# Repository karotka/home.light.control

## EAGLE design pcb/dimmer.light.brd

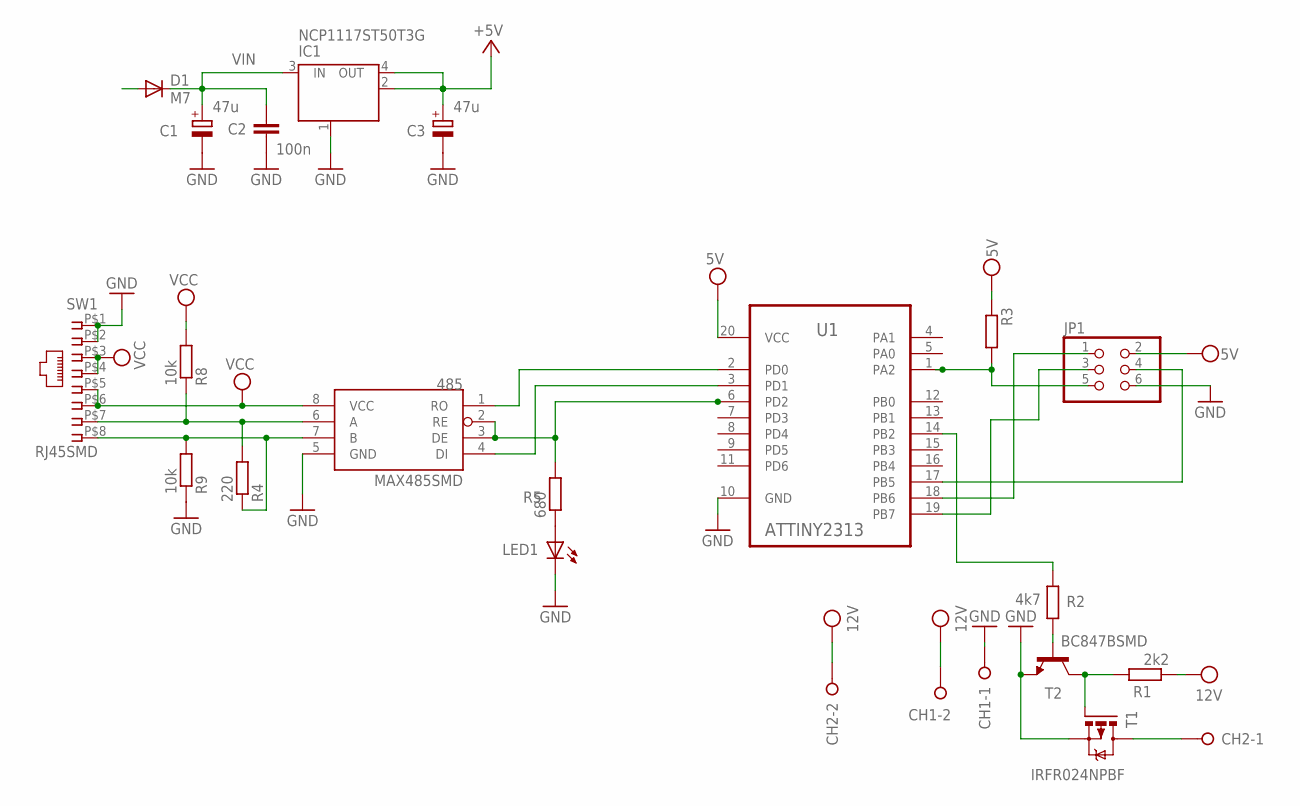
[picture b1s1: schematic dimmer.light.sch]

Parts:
485: MAX485SMD; SO08
C1, C3: 47u; PANASONIC_D
C2: 100n; C1206
CH1, CH2: W237-02P; W237-132
D1: M7; SMB
IC1: NCP1117ST50T3G; SOT223
JP1: PINHD-2X3; 2X03
LED1: LEDSML1206; SML1206
R1: 2k2; R1206
R2: 4k7; R1206
R3: R-EU_R1206; R1206
R4: 220; R1206
R5: 680; R1206
R8, R9: 10k; R1206
SW1: RJ45SMD
T1: IRFR024NPBF; D-PAK_TO252AA
T2: BC847BSMD; SOT23
U1: ATTINY2313; SOIC127P1032X265-20N

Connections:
A: 485.6 (A), R4.2, R8.1, SW1.P$7 (7)
B: 485.7 (B), R4.1, R9.2, SW1.P$8 (8)
GND: 485.5 (GND), C1.-, C2.2, C3.-, CH1.1, IC1.1 (GND/ADJ), JP1.6, LED1.C, R9.1, SW1.P$1 (1), SW1.P$2 (2), T1.3 (S), T2.2 (E), U1.10 (GND)
unnamed: R2.1, T2.1 (B)
unnamed: JP1.3, U1.19 (PB7)
unnamed: JP1.1, U1.18 (PB6)
unnamed: JP1.4, U1.17 (PB5)
unnamed: R1.2, T1.1 (G), T2.3 (C)
unnamed: R2.2, U1.14 (PB2)
unnamed: CH2.1, T1.4 (D)
unnamed: 485.4 (DI), U1.3 (PD1)
unnamed: 485.1 (RO), U1.2 (PD0)
unnamed: 485.2 (RE), 485.3 (DE), R5.2, U1.6 (PD2)
unnamed: JP1.5, R3.2, U1.1 (PA2)
unnamed: LED1.A, R5.1
PWRIN: CH1.2, CH2.2, D1.A, R1.1
VCC+5V: 485.8 (VCC), C3.+, IC1.2 (OUT), IC1.4 (OUT), JP1.2, R3.1, R8.2, SW1.P$5 (5), SW1.P$6 (6), U1.20 (VCC)
VIN: C1.+, C2.1, D1.C, IC1.3 (IN), SW1.P$3 (3), SW1.P$4 (4)

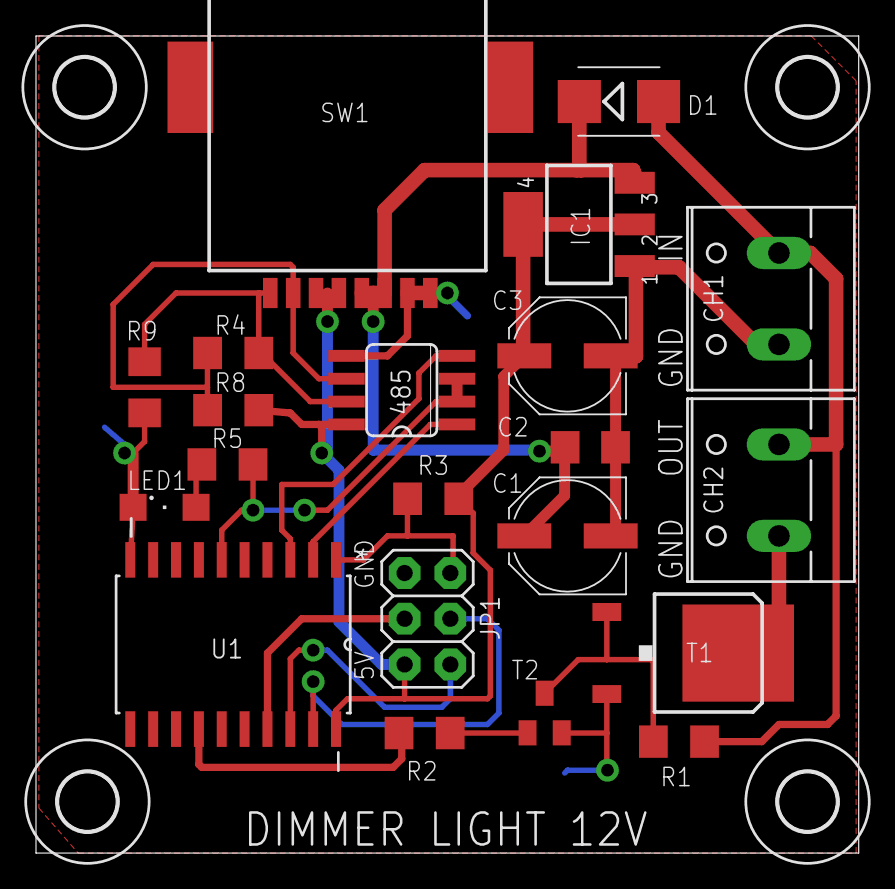
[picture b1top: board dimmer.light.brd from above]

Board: 2 copper layers, 45.7 x 45.4 mm, 25 parts (0 on the bottom side), 18 nets.

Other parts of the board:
U$1, U$2, U$3, U$4: 3,2

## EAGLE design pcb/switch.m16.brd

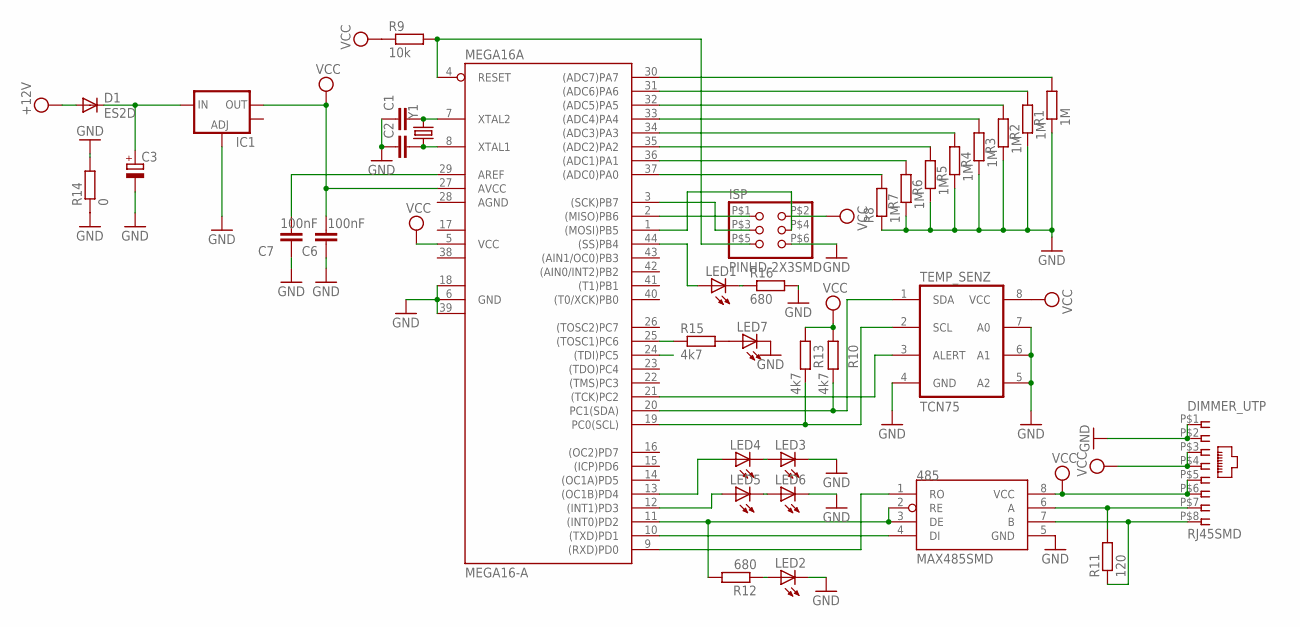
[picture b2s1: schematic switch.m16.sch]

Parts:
485: MAX485SMD; SO08
C1, C2: C-EUC0805; C0805
C3: CPOL-EUSMCC; SMC_C
C6, C7: 100nF; C1206
D1: ES2D; SMB
DIMMER_UTP: RJ45SMD
IC1: V_REG_LM1117SOT223; SOT223
ISP: PINHD-2X3SMD; 2X03SMD
LED1, LED2, LED3, LED4, LED5, LED6, LED7: LEDSML1206; SML1206
MEGA16A: MEGA16-A; TQFP44
R1, R2, R3, R4, R5, R6, R7, R8: 1M; R1206
R9: 10k; R1206
R10, R13, R15: 4k7; R1206
R11: 120; R1206
R12, R16: 680; R1206
R14: 0; R1206
TEMP_SENZ: TCN75; SO08
Y1: CRYSTAL5X3; CRYSTAL-SMD-5X3

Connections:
+12V: D1.A, DIMMER_UTP.P$3 (3), DIMMER_UTP.P$4 (4)
AGND: MEGA16A.28 (AGND)
GND: 485.5 (GND), C1.1, C2.1, C3.-, C6.1, C7.2, DIMMER_UTP.P$1 (1), DIMMER_UTP.P$2 (2), IC1.1 (ADJ), ISP.P$6 (6), LED2.C, LED3.C, LED6.C, LED7.C, MEGA16A.6 (GND), MEGA16A.18 (GND1), MEGA16A.39 (GND2), R1.1, R2.1, R3.1, R4.1, R5.1, R6.1, R7.1, R8.1, R14.1, R14.2, R16.2, TEMP_SENZ.4 (GND), TEMP_SENZ.5 (A2), TEMP_SENZ.6 (A1), TEMP_SENZ.7 (A0)
unnamed: LED4.A, MEGA16A.13 ((OC1B)PD4)
unnamed: LED1.A, MEGA16A.44 ((SS)PB4)
unnamed: C3.+, D1.C, IC1.3 (IN)
unnamed: MEGA16A.31 ((ADC6)PA6), R2.2
unnamed: MEGA16A.30 ((ADC7)PA7), R1.2
unnamed: MEGA16A.37 ((ADC0)PA0), R8.2
unnamed: MEGA16A.34 ((ADC3)PA3), R5.2
unnamed: MEGA16A.35 ((ADC2)PA2), R6.2
unnamed: MEGA16A.25 ((TOSC1)PC6), R15.1
unnamed: MEGA16A.19 (PC0(SCL)), R13.2, TEMP_SENZ.2 (SCL)
unnamed: MEGA16A.20 (PC1(SDA)), R10.2, TEMP_SENZ.1 (SDA)
unnamed: MEGA16A.21 ((TCK)PC2), TEMP_SENZ.3 (ALERT)
unnamed: LED7.A, R15.2
unnamed: 485.1 (RO), MEGA16A.9 ((RXD)PD0)
unnamed: 485.4 (DI), MEGA16A.10 ((TXD)PD1)
unnamed: 485.2 (RE), 485.3 (DE), MEGA16A.11 ((INT0)PD2), R12.2
unnamed: LED5.A, MEGA16A.12 ((INT1)PD3)
unnamed: ISP.P$1 (1), MEGA16A.2 ((MISO)PB6)
unnamed: ISP.P$3 (3), MEGA16A.3 ((SCK)PB7)
unnamed: ISP.P$5 (5), MEGA16A.4 (RESET), R9.2
unnamed: ISP.P$4 (4), MEGA16A.1 ((MOSI)PB5)
unnamed: 485.6 (A), DIMMER_UTP.P$7 (7), R11.2
unnamed: 485.7 (B), DIMMER_UTP.P$8 (8), R11.1
unnamed: C1.2, MEGA16A.7 (XTAL2), Y1.3 (2)
unnamed: C2.2, MEGA16A.8 (XTAL1), Y1.1
unnamed: LED2.A, R12.1
unnamed: MEGA16A.33 ((ADC4)PA4), R4.2
unnamed: LED1.C, R16.1
unnamed: MEGA16A.32 ((ADC5)PA5), R3.2
unnamed: MEGA16A.36 ((ADC1)PA1), R7.2
unnamed: C7.1, MEGA16A.29 (AREF)
unnamed: LED3.A, LED4.C
unnamed: LED5.C, LED6.A
PC5: MEGA16A.24 ((TDI)PC5)
VCC: 485.8 (VCC), C6.2, DIMMER_UTP.P$5 (5), DIMMER_UTP.P$6 (6), IC1.2 (OUT), ISP.P$2 (2), MEGA16A.5 (VCC), MEGA16A.27 (AVCC), R9.1, R10.1, R13.1, TEMP_SENZ.8 (VCC)
VCC1: MEGA16A.17 (VCC1)
VCC2: MEGA16A.38 (VCC2)

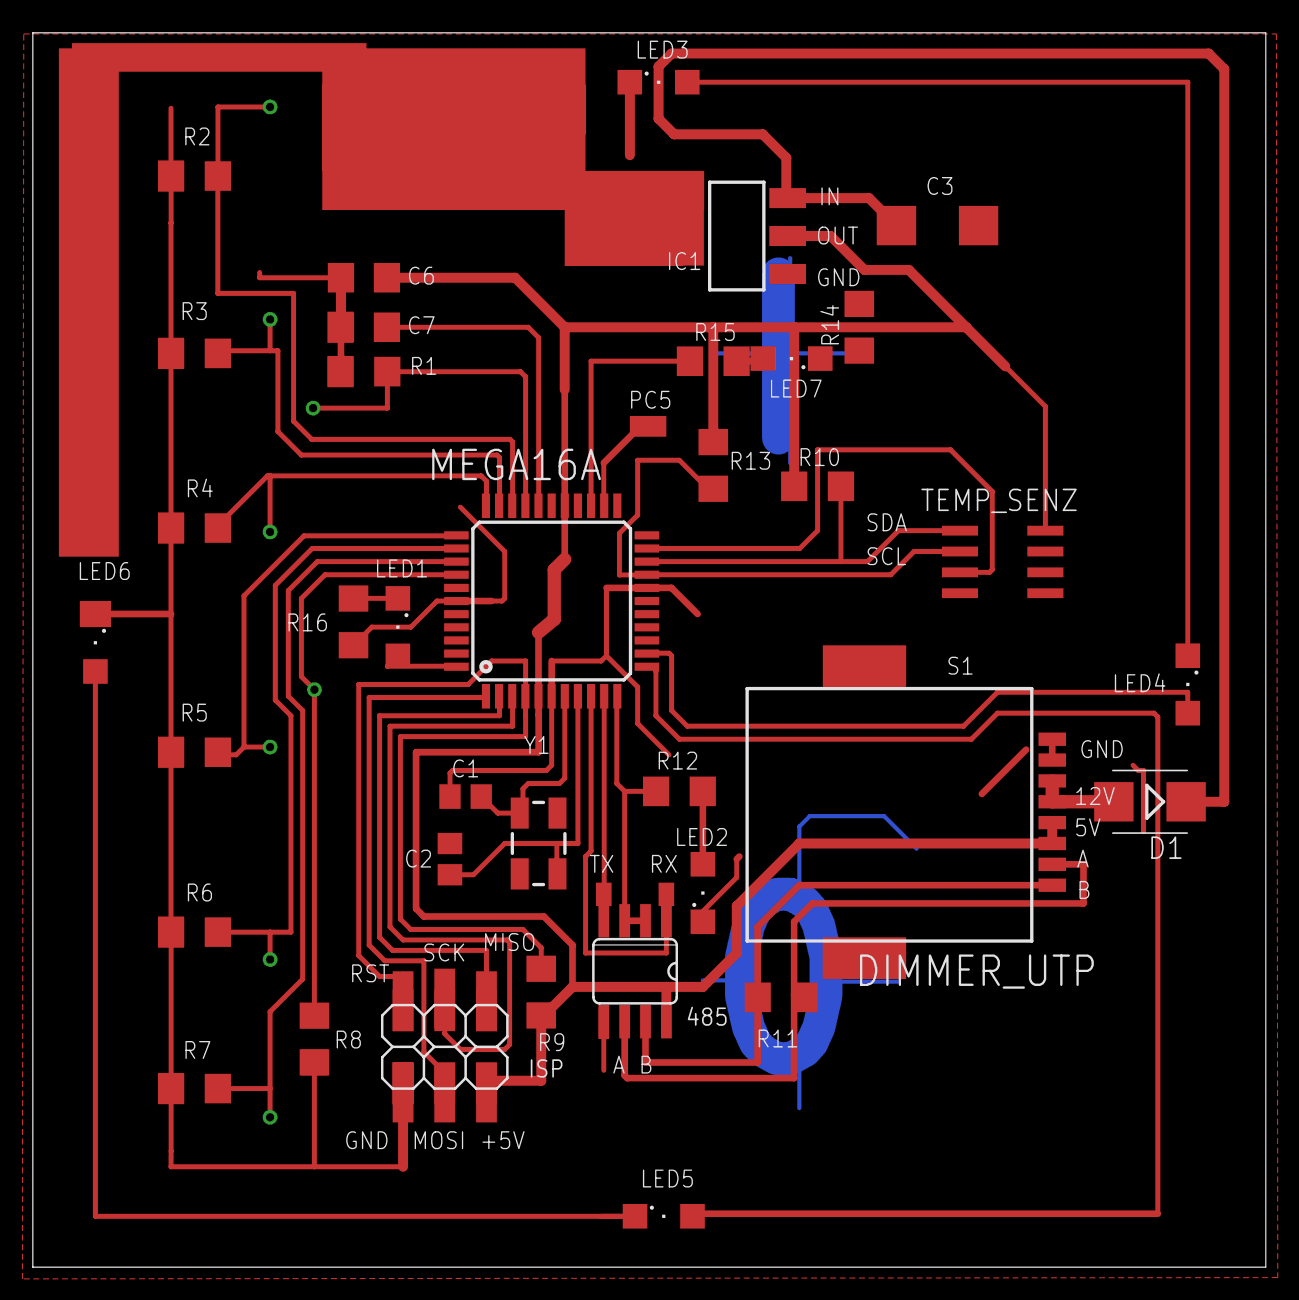
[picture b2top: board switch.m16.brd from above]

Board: 2 copper layers, 75.1 x 75.2 mm, 36 parts (0 on the bottom side), 36 nets.

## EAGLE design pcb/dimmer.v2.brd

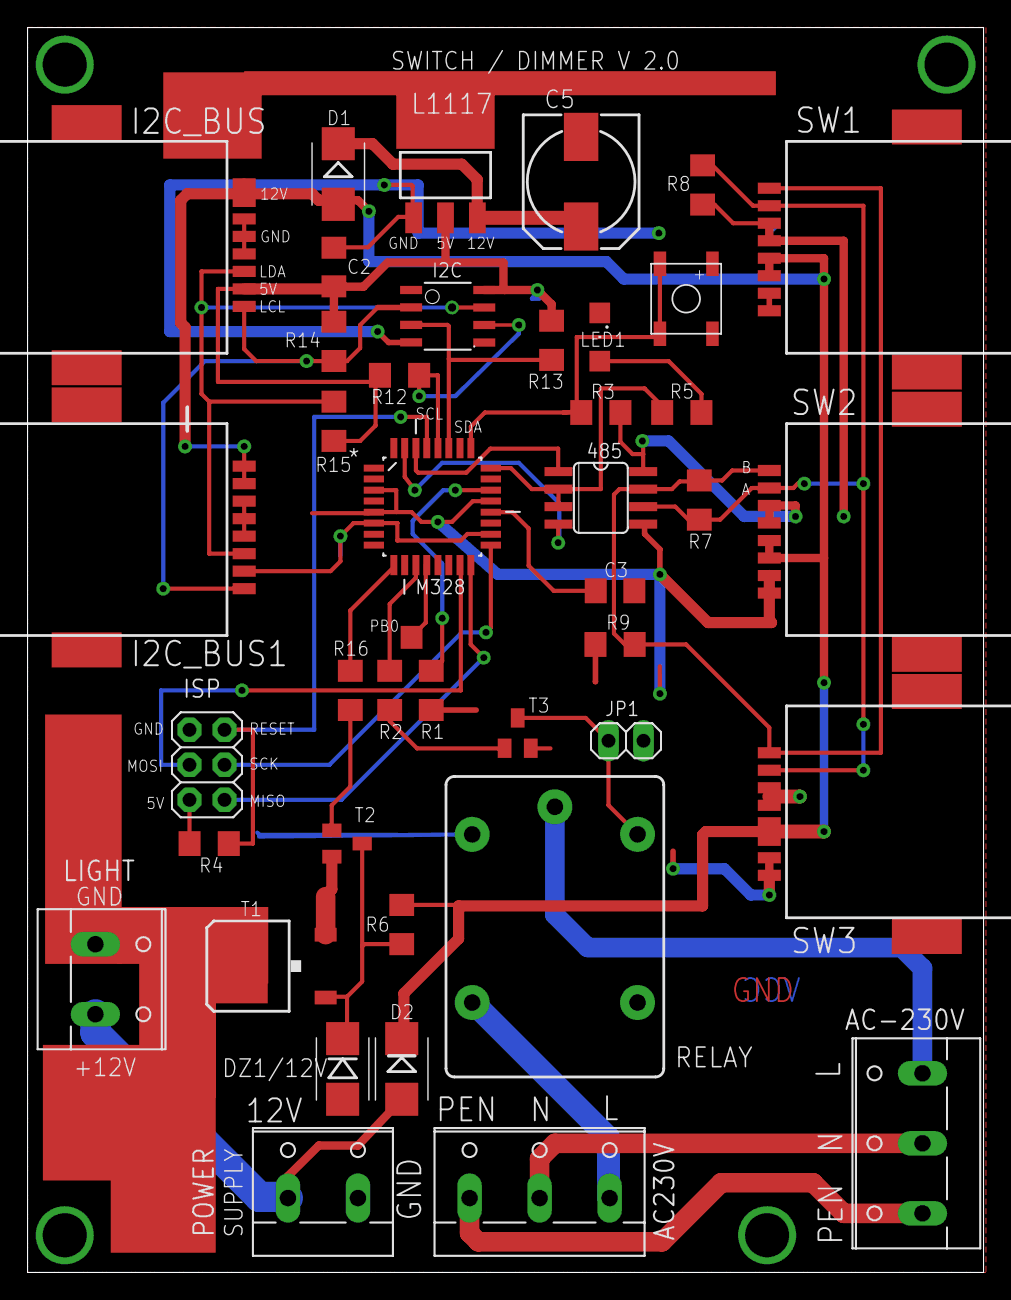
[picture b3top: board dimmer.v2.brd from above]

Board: 2 copper layers, 69.4 x 90.3 mm, 41 parts (0 on the bottom side), 33 nets.

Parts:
485: MAX485SMD; SO08
AC230V: W237-3E
AC-230V: W237-3E
C2, C3: 100nF; C1206
C5: 100uF; 140CLH-0810
D1, D2: M1; SMB
DZ1/12V: DIODE-ZENERSMB; SMB-DIODE
I2C: P82B715; P82B715SMD
I2C_BUS, I2C_BUS1: RJ45SMD
ISP: 2X03
JP1: 1X02
L1117: SOT223
LED1: SML1206
LIGHT: W237-132
M328: ATMEGA328P-AU; QFP80P900X900X120-32N
POWER: W237-132
PROG: MIMISMD; MINISMD
R1, R3, R4, R8, R9: 10k; R1206
R2, R5, R16: 680; R1206
R6: 1K; R1206
R7: 120; R1206
R12, R13: 4k7; R1206
R14, R15: 470; R1206
RELAY: JS-M1-9V-4; JS-M
SW1, SW2, SW3: RJ45SMD
T1: IRFR5305; D-PAK_TO252AA
T2, T3: BC847BSMD; SOT23

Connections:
12V: D2.A, LIGHT.2, POWER.1
+12V: D1.A, D2.C, I2C_BUS.P$1, I2C_BUS.P$2, I2C_BUS1.P$1, I2C_BUS1.P$2, R6.1, SW1.P$3, SW1.P$4, SW2.P$3, SW2.P$4, SW3.P$3, SW3.P$4
A: 485.6, R7.2, R8.1, SW1.P$7, SW2.P$7, SW3.P$7
B: 485.7, R7.1, R9.2, SW1.P$8, SW2.P$8, SW3.P$8
GND: 485.5, C2.2, C3.2, C5.-, DZ1/12V.A, I2C.4, I2C_BUS.P$3, I2C_BUS.P$4, I2C_BUS.P$5, I2C_BUS1.P$3, I2C_BUS1.P$4, I2C_BUS1.P$5, ISP.6, JP1.1, L1117.1, LED1.C, M328.3, M328.5, M328.21, POWER.2, PROG.P$2, PROG.P$4, R1.1, R9.1, SW1.P$1, SW1.P$2, SW2.P$1, SW2.P$2, SW3.P$1, SW3.P$2, T1.3, T2.2, T3.2
IN: C5.+, D1.C, L1117.3
LX: I2C.2, I2C_BUS.P$8, I2C_BUS1.P$8, R14.2
LY: I2C.7, I2C_BUS.P$6, I2C_BUS1.P$6, R15.2
MISO: ISP.1, M328.16
MOSI: ISP.4, M328.15
unnamed: R16.1, T2.1
unnamed: 485.4, M328.31
unnamed: 485.1, M328.30
unnamed: M328.25, PROG.P$1, PROG.P$3, R3.1
unnamed: M328.9, R16.2
unnamed: AC230V.3, RELAY.NO
unnamed: AC230V.1, AC-230V.1
unnamed: AC230V.2, AC-230V.2
unnamed: DZ1/12V.C, R6.2, T1.1, T2.3
unnamed: R2.2, T3.1
unnamed: LIGHT.1, T1.4
unnamed: AC-230V.3, RELAY.C
unnamed: 485.2, 485.3, M328.24, R5.2
unnamed: M328.22, R1.2
unnamed: M328.11, R2.1
unnamed: C3.1, M328.20
unnamed: JP1.2, RELAY.2, T3.3
unnamed: LED1.A, R5.1
RESET: ISP.5, M328.29, R4.2
SCK: ISP.3, M328.17
SCL: I2C.6, M328.28, R12.1
SDA: I2C.3, M328.27, R13.1
VCC: 485.8, C2.1, I2C.8, I2C_BUS.P$7, I2C_BUS1.P$7, ISP.2, L1117.2, M328.6, M328.18, R3.2, R4.1, R8.2, R12.2, R13.2, R14.1, R15.1, RELAY.1, SW1.P$5, SW1.P$6, SW2.P$5, SW2.P$6, SW3.P$5, SW3.P$6

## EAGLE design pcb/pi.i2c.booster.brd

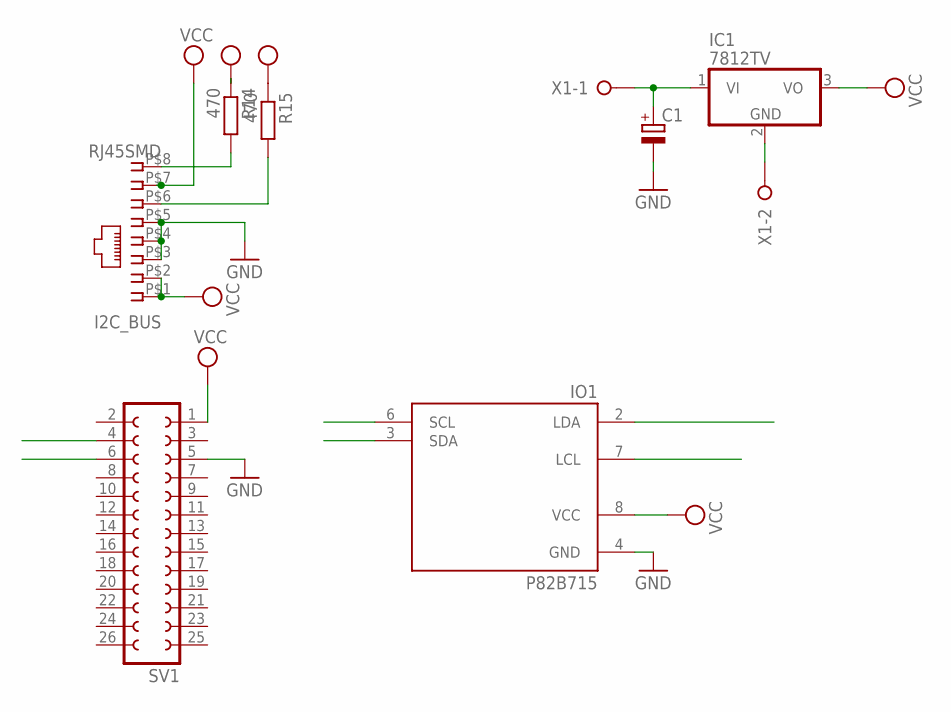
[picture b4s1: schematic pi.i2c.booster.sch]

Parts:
C1: CPOL-EUB45181B; B45181B
I2C_BUS: RJ45SMD
IC1: 7812TV; TO220V
IO1: P82B715; P82B715SMD
R14, R15: 470; R1206
SV1: FE13-2
X1: W237-02P; W237-132

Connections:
+12V: C1.+, I2C_BUS.P$1 (1), I2C_BUS.P$2 (2), IC1.1 (VI), X1.1
GND: C1.-, I2C_BUS.P$3 (3), I2C_BUS.P$4 (4), I2C_BUS.P$5 (5), IC1.2 (GND), IO1.4 (GND), SV1.5, X1.2
LX: I2C_BUS.P$8 (8), IO1.2 (LDA), R14.2
LY: I2C_BUS.P$6 (6), IO1.7 (LCL), R15.2
SCL: IO1.6 (SCL), SV1.6
SDA: IO1.3 (SDA), SV1.4
VCC: I2C_BUS.P$7 (7), IC1.3 (VO), IO1.8 (VCC), R14.1, R15.1, SV1.1

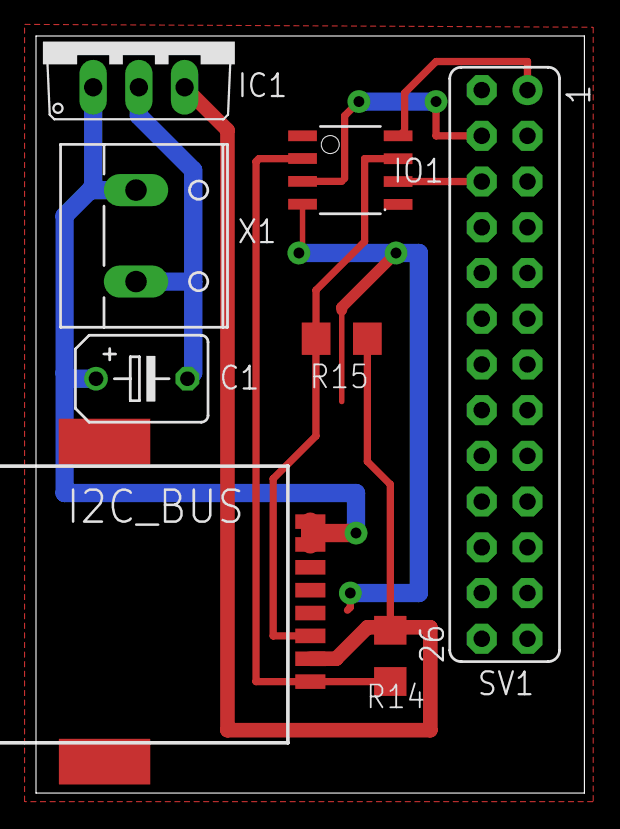
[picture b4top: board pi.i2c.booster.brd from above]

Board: 2 copper layers, 30.5 x 42.1 mm, 8 parts (0 on the bottom side), 7 nets.

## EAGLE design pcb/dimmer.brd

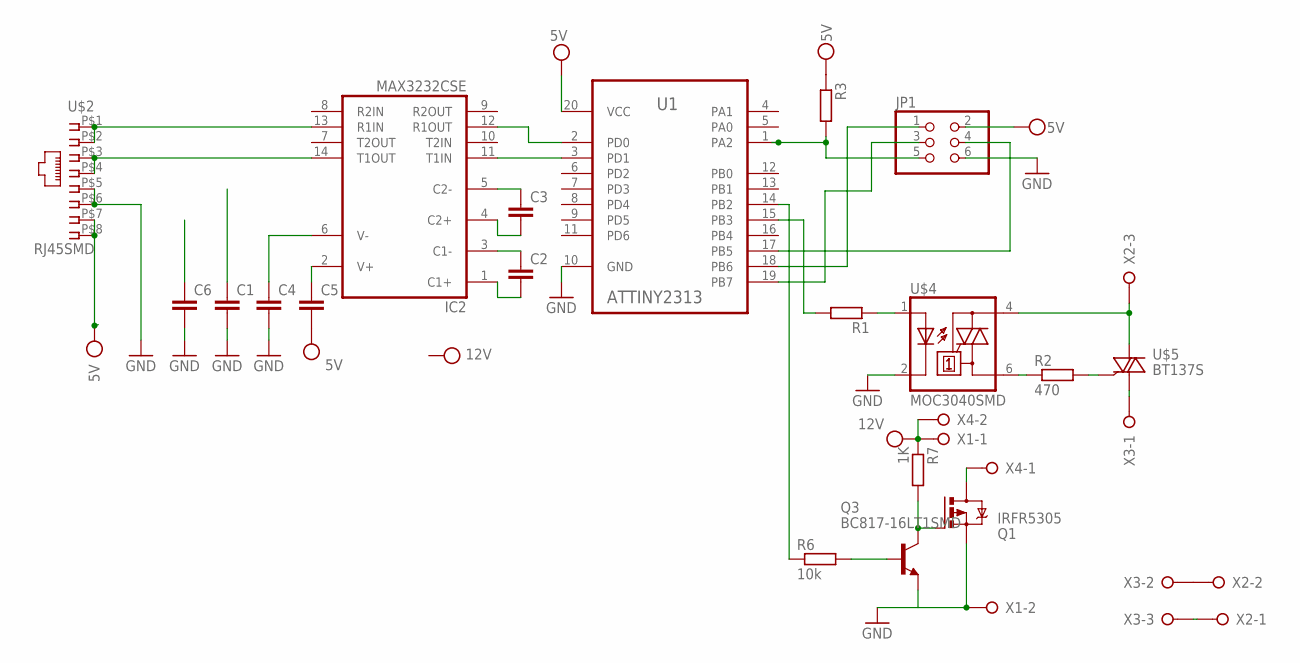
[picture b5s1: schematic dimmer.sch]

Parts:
C1, C6: C-EUC1206; C1206
C2, C3, C4, C5: C-EUC0603; C0603
IC2: MAX3232CSE; SO16
JP1: PINHD-2X3; 2X03
Q1: IRFR5305; D-PAK_TO252AA
Q3: BC817-16LT1SMD; SOT23-BEC
R1, R3: R-EU_R1206; R1206
R2: 470; R1206
R6: 10k; R1206
R7: 1K; R1206
U1: ATTINY2313; SOIC127P1032X265-20N
U$2: RJ45SMD
U$4: MOC3040SMD; DIL6-SMD
U$5: BT137S; DPACK
X1, X4: W237-02P; W237-132
X2, X3: W237-3E

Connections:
GND: C1.2, C4.2, C6.2, IC2.15 (GND), JP1.6, Q1.3 (S), Q3.E, U1.10 (GND), U$2.P$5 (5), U$2.P$6 (6), U$4.2 (C), X1.2
unnamed: R2.2, U$5.3 (G)
unnamed: Q3.B, R6.2
unnamed: IC2.13 (R1IN), U$2.P$1 (1), U$2.P$2 (2)
unnamed: IC2.14 (T1OUT), U$2.P$3 (3), U$2.P$4 (4)
unnamed: JP1.3, U1.19 (PB7)
unnamed: JP1.1, U1.18 (PB6)
unnamed: JP1.4, U1.17 (PB5)
unnamed: IC2.12 (R1OUT), U1.2 (PD0)
unnamed: R1.1, U$4.1 (A)
unnamed: IC2.11 (T1IN), U1.3 (PD1)
unnamed: Q1.1 (G), Q3.C, R7.2
unnamed: R6.1, U1.14 (PB2)
unnamed: R1.2, U1.15 (PB3)
unnamed: Q1.4 (D), X4.1
unnamed: X2.1, X3.3
unnamed: X2.2, X3.2
unnamed: U$5.1 (A1), X3.1
unnamed: U$4.4 (A2), U$5.2 (A2), X2.3
unnamed: R2.1, U$4.6 (A1)
unnamed: C3.1, IC2.5 (C2-)
unnamed: C3.2, IC2.4 (C2+)
unnamed: C2.1, IC2.3 (C1-)
unnamed: C2.2, IC2.1 (C1+)
unnamed: C4.1, IC2.6 (V-)
unnamed: C5.1, IC2.2 (V+)
unnamed: JP1.5, R3.2, U1.1 (PA2)
VCC+5V: C1.1, C5.2, IC2.16 (VCC), JP1.2, R3.1, U1.20 (VCC), U$2.P$7 (7), U$2.P$8 (8)
VCC+12V: C6.1, R7.1, X1.1, X4.2

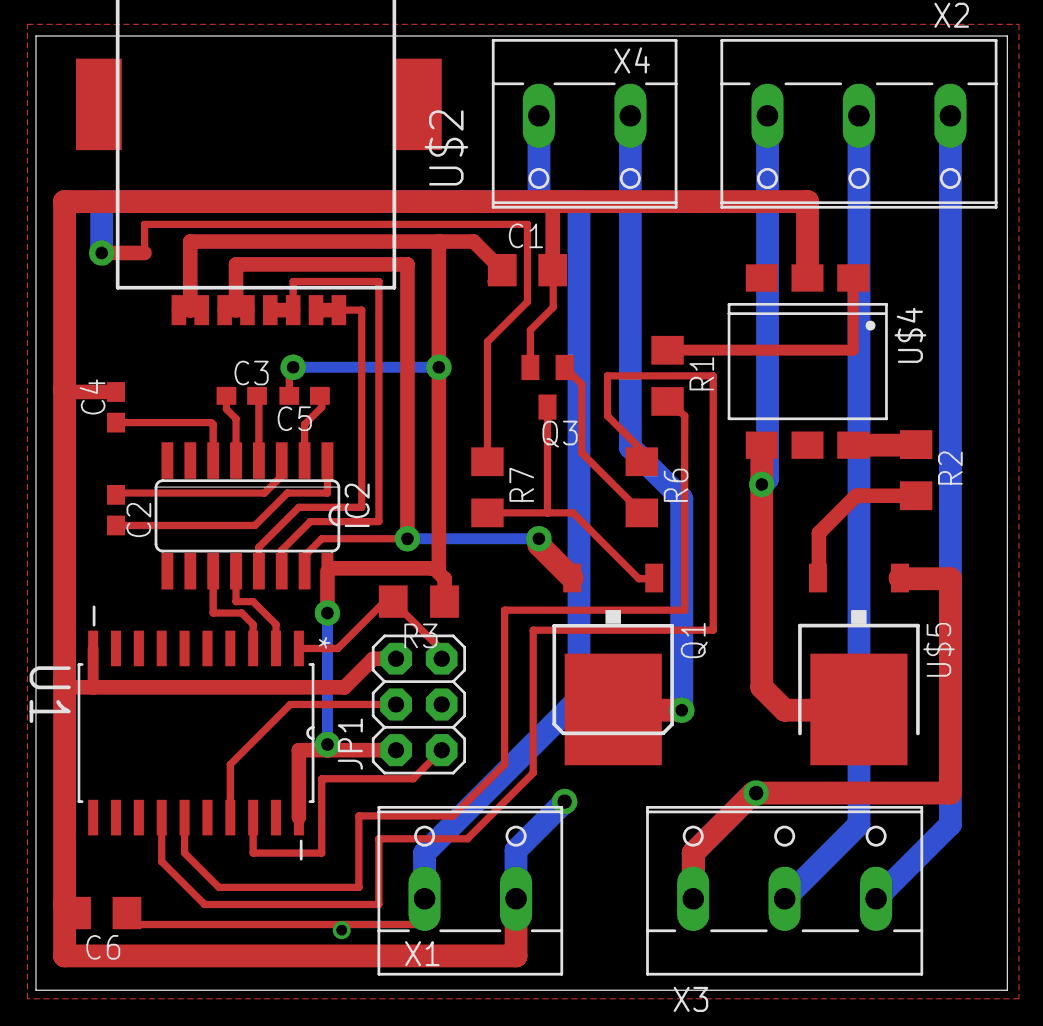
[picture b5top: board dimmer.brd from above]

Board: 2 copper layers, 54.0 x 53.0 mm, 23 parts (0 on the bottom side), 29 nets.

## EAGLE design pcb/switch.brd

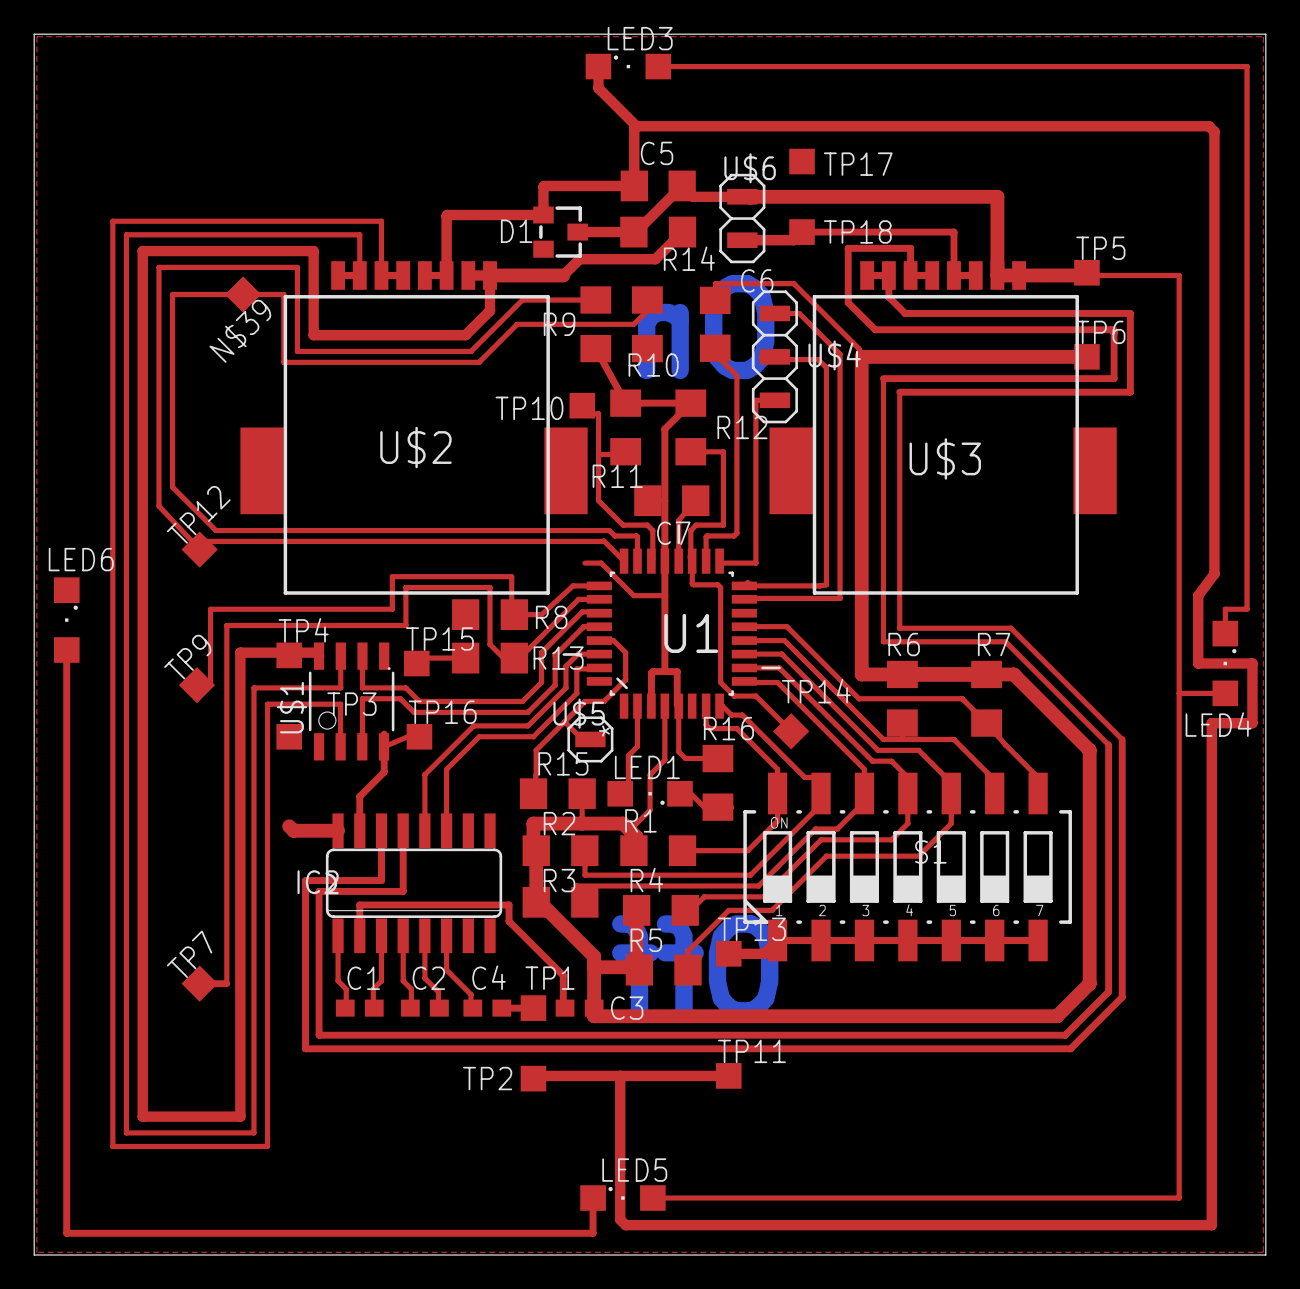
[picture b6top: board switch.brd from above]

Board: 2 copper layers, 72.1 x 71.4 mm, 56 parts (0 on the bottom side), 41 nets.

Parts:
C1, C2, C3, C4: C0603
C5, C6, C7: C1206
D1: BZX84CSMD; TO236
IC2: MAX3232CSE; SO16
LED1, LED3, LED4, LED5, LED6: SML1206
N$39: TPSQTP15SQ; TP15SQ
R1, R2, R3, R4, R5, R6, R7, R8, R9, R10, R11, R12, R13, R14, R15, R16: R1206
S1: 219-07; CTS-219-07
TP1, TP2, TP3, TP4, TP5, TP6, TP7, TP9, TP10, TP11, TP12, TP13, TP14, TP15, TP16, TP17, TP18: TPSQTP15SQ; TP15SQ
U1: ATMEGA48-20AU; QFP80P900X900X120-32N
U$1: P82B715; P82B715SMD
U$2, U$3: RJ45SMD
U$4: 1X03SMD
U$5: PINHD-1X1SMD; 1X01SMD
U$6: PINHD-1X2SMD; 1X02SMD

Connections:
+12V: IC2.16, R14.1, U$1.8, U$2.P$7, U$2.P$8
GND: C4.2, C5.2, C7.2, D1.A, IC2.15, LED3.C, LED6.C, R8.2, R9.2, R10.2, R11.2, R12.2, R13.2, R16.2, S1.1, S1.2, S1.3, S1.4, S1.5, S1.6, S1.7, TP2.TP, TP11.TP, TP13.TP, TP15.TP, TP16.TP, TP17.TP, TP18.TP, U1.3, U1.5, U1.21, U$1.4, U$2.P$5, U$2.P$6, U$3.P$5, U$3.P$6, U$6.P$2
unnamed: U1.28, U$1.3
unnamed: U1.27, U$1.6
unnamed: R1.2, S1.14, U1.7
unnamed: R7.2, S1.8, U1.13
unnamed: R6.2, S1.9, U1.12
unnamed: R5.2, S1.10, U1.11
unnamed: R4.2, S1.11, U1.10
unnamed: R3.2, S1.12, U1.9
unnamed: R2.2, S1.13, U1.8
unnamed: IC2.11, U1.31
unnamed: IC2.12, U1.30
unnamed: U$1.7, U$2.P$1, U$2.P$2
unnamed: U$1.2, U$2.P$3, U$2.P$4
unnamed: R12.1, TP14.TP, U1.19
unnamed: R11.1, TP10.TP, U1.22
unnamed: N$39.TP, R10.1, U1.23
unnamed: R9.1, TP12.TP, U1.24
unnamed: R8.1, TP9.TP, U1.25
unnamed: R13.1, TP7.TP, U1.26
unnamed: C1.1, IC2.1
unnamed: C3.1, C5.1, C6.1, D1.C, LED4.A, LED5.A, R1.1, R2.1, R3.1, R4.1, R5.1, R6.1, R7.1, R14.2, R15.2, TP5.TP, TP6.TP, U1.4, U1.6, U$3.P$7, U$3.P$8, U$6.P$1
unnamed: C1.2, IC2.3
unnamed: IC2.14, U$3.P$1, U$3.P$2
unnamed: IC2.13, U$3.P$3, U$3.P$4
unnamed: C2.1, IC2.4
unnamed: C2.2, IC2.5
unnamed: C3.2, IC2.2
unnamed: C4.1, IC2.6
unnamed: U1.17, U$4.P$1
unnamed: U1.16, U$4.P$2
unnamed: U1.15, U$4.P$3
unnamed: R15.1, U1.29, U$5.P$1
unnamed: LED1.C, R16.1
unnamed: C6.2, U1.18
unnamed: LED1.A, U1.2
unnamed: C7.1, U1.20
unnamed: LED3.A, LED4.C
unnamed: LED5.C, LED6.A
VCC: TP3.TP, TP4.TP

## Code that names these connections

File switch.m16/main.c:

#include <avr/io.h>
#include <avr/interrupt.h>
#include <avr/sleep.h>
#include <avr/power.h>
#include <util/delay.h>
#include <stdio.h>
#include "uart.h"
#include "touch.h"
//#include "twi.h"


static touch_channel_t btn0 = {
    .mux = 0,
    .port = &PORTA,
    .portmask = (1 << PA0),
    .state = btnOff,
    .limit = 170,
};
static touch_channel_t btn1 = {
    .mux = 1,
    .port = &PORTA,
    .portmask = (1 << PA1),
    .state = btnOff,
    .limit = 90,
};
static touch_channel_t btn2 = {
    .mux = 2,
    .port = &PORTA,
    .portmask = (1 << PA2),
    .state = btnOff,
    .limit = 90,
};
static touch_channel_t btn3 = {
    .mux = 3,
    .port = &PORTA,
    .portmask = (1 << PA3),
    .state = btnOff,
    .limit = 90,
};
static touch_channel_t btn4 = {
    .mux = 4,
    .port = &PORTA,
    .portmask = (1 << PA4),
    .state = btnOff,
    .limit = 90,
};
static touch_channel_t btn5 = {
    .mux = 5,
    .port = &PORTA,
    .portmask = (1 << PA5),
    .state = btnOff,
    .limit = 90,
};
static touch_channel_t btn6 = {
    .mux = 6,
    .port = &PORTA,
    .portmask = (1 << PA6),
    .state = btnOff,
    .limit = 90,
};
static touch_channel_t btn7 = {
    .mux = 7,
    .port = &PORTA,
    .portmask = (1 << PA7),
    .state = btnOff,
    .limit = 170,
};


void watchDogInit(void);
void pinsInit(void);
void pinsInit(void);
void timer0Init(void);

volatile int value = 0;
volatile uint8_t send = 0;

void handleButtons(void) {
    btn_set(&btn0);
    btn_set(&btn1);
    btn_set(&btn2);
    btn_set(&btn3);
    btn_set(&btn4);
    btn_set(&btn5);
    btn_set(&btn6);
    btn_set(&btn7);

    if (btn1.state == btnOn) {
        send = 1;
        if (btn2.state == btnOn) {
            value = 2;
            return;
        } else {
            value = 1;
            return;
        }
    }

    if (btn2.state == btnOn) {
        send = 1;
        if (btn3.state == btnOn) {
            value = 4;
            return;
        } else {
            value = 3;
            return;
        }
    }

    if (btn3.state == btnOn) {
        send = 1;
        if (btn4.state == btnOn) {
            value = 6;
            return;
        } else {
            value = 5;
            return;
        }
    }

    if (btn4.state == btnOn) {
        send = 1;
        if (btn5.state == btnOn) {
            value = 8;
            return;
        } else {
            value = 7;
            return;
        }
    }

    if (btn5.state == btnOn) {
        send = 1;
        if (btn6.state == btnOn) {
            value = 10;
            return;
        } else {
            value = 9;
            return;
        }
    }

    if (btn6.state == btnOn) {
        send = 1;
        value = 11;
        return;
    }

    if (btn7.state == btnOn) {
        send = 1;
        value = 16;
        return;
    }

    // handle off
    if (btn0.state == btnRelease) {
        send = 1;
        value = 0;
        return;
    }
}

ISR(TIMER0_OVF_vect) {
    handleButtons();
}

void timer0Init(void) {
    // Set the Timer Mode to OVF
    TIMSK |= (1 << TOIE0);
    TCCR0 |= (1 << CS00) | (1 << CS02); // / 1024
}

int main(void) {

    pinsInit();
    timer0Init();

    _delay_ms(200);
    sei();

    // Start UART
    UART_init();

    // Init ADC touch library
    TOUCH_init();

    uint8_t i;

    //char chr[100];
    //uint16_t val;

    for(;;) {

        //sprintf (chr, "0: %d, 1: %d, 2: %d, 3: %d, 4: %d, 5: %d, 6: %d, 7: %d \n",
        //    btn0.state, btn1.state, btn2.state, btn3.state, btn4.state, btn5.state, btn6.state, btn7.state);
        //UART_puts(chr);

        //sprintf (chr, "0: %d, 1: %d, 2: %d, 3: %d, 4: %d, 5: %d, 6: %d, 7: %d \n",
        //    btn0.sum, btn1.sum, btn2.sum, btn3.sum, btn4.sum, btn5.sum, btn6.sum, btn7.sum);
        //UART_puts(chr);
        //UART_puts("\n");
        //_delay_ms(100);
        if (send == 1) {
            // high - enable trancseiver
            PORTD |= (1 << PD2);
            for (i = 0; i < 5; i++) {
                PORTB ^= (1 << PB4);
                UART_putc((char)value);
                _delay_ms(20);
            }
            send = 0;
        }
        // low - enable receiver
        PORTD &= ~(1 << PD2);

        // switch off background light
        if (value == 0) {
            PORTC |= (1 << PC6);
        } else {
            PORTC &= ~(1 << PC6);
        }
    }
}

void pinsInit(void) {
    // all B pins as input
    DDRB = 0x00;
    PORTB = 0x00;
    DDRB |= (1 << PB4);

    DDRC = 0x00;
    PORTC = 0x00;

    DDRC  |= (1 << PC6);

    DDRD = 0x00;
    PORTD = 0x00;

    //DDRD  |= (1 << PD3) | (1 << PD4);
    DDRD  |= (1 << PD2);
}

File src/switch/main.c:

#define F_CPU 8000000UL
#include <avr/io.h>
#include <avr/interrupt.h>
#include <avr/sleep.h>
#include <avr/power.h>
#include <util/delay.h>
#include "uart.h"
#include "touch.h"
//#include "twi.h"


static touch_channel_t btn1 = {
    .mux = 0,
    .port = &PORTC,
    .portmask = (1 << PC0),
    .state = btnOff,
    .count = 0,
};
static touch_channel_t btn2 = {
    .mux = 1,
    .port = &PORTC,
    .portmask = (1 << PC1),
    .state = btnOff,
    .count = 0,
};
static touch_channel_t btn3 = {
    .mux = 2,
    .port = &PORTC,
    .portmask = (1 << PC2),
    .state = btnOff,
    .count = 0,
};
static touch_channel_t btn4 = {
    .mux = 3,
    .port = &PORTC,
    .portmask = (1 << PC3),
    .state = btnOff,
    .count = 0,
};
static touch_channel_t btn5 = {
    .mux = 4,
    .port = &PORTC,
    .portmask = (1 << PC4),
    .state = btnOff,
    .count = 0,
};
static touch_channel_t btn6 = {
    .mux = 5,
    .port = &PORTC,
    .portmask = (1 << PC5),
    .state = btnOff,
    .count = 0,
};

void watchDogInit(void);
void pinsInit(void);
void pinsInit(void);
void timer0Init(void);
//void readAddress(volatile uint8_t *port, volatile uint8_t *addr);

volatile uint8_t value = 0;
volatile uint8_t lastValue = 0;
volatile uint8_t sleepValue = 9;
volatile uint8_t count = 0;
volatile uint8_t sleep = 1;

void handleButtons(void) {
    btn_set(&btn1);
    btn_set(&btn2);
    btn_set(&btn3);
    btn_set(&btn4);
    btn_set(&btn6);

    if (btn1.state == btnOn) {
        if (btn2.state == btnOn) {
            value = 6;
            return;
        } else {
            value = 7;
            return;
        }
    }

    if (btn2.state == btnOn) {
        if (btn3.state == btnOn) {
            value = 4;
            return;
        } else {
            value = 5;
            return;
        }
    }

    if (btn3.state == btnOn) {
        if (btn4.state == btnOn) {
            value = 2;
            return;
        } else {
            value = 3;
            return;
        }
    }

    if (btn4.state == btnOn) {
        value = 1;
        return;
    }

    // handle off
    if (btn6.state == btnRelease) {
        value = 0;
        sleep = 1;
        return;
    }
}

void sleepMode(void) {
    set_sleep_mode(SLEEP_MODE_PWR_SAVE);//SLEEP_MODE_PWR_DOWN);
    cli();
    sleep_enable();
    sei();
    sleep_cpu();
    sleep_mode();
    sleep_disable();
    power_all_enable();
}

ISR(WDT_vect) {
    // hadle on
    btn_set(&btn5);

    if (btn5.state == btnRelease) {
        value = sleepValue;
        sleep = 0;
    }

    if (sleep == 0) {
        handleButtons();
    }
}

void timer0Init(void) {
    // Set the Timer Mode to CTC
    TIFR0 |= (1 << TOV0);
    TIMSK0 |= (1 << TOIE0);
    TCNT0 = 255;
    TCCR0B |= (1 << CS00) | (1 << CS02);
}

int main(void) {
    //volatile uint8_t TWI_slaveAddress;

    pinsInit();
    watchDogInit();
    //pwmInit();
    //timer0Init();

    //readAddress(&PINB, &TWI_slaveAddress);
    //TWI_slaveAddress = 0x20;

    _delay_ms(200);
    sei();

    // Initialise TWI module for slave operation
    //TWI_SlaveInitialise(TWI_slaveAddress << TWI_ADR_BITS);
    // Start the TWI transceiver
    //TWI_StartTransceiver();

    // Start UART
    UART_init();

    // Init ADC touch library
    TOUCH_init();

    //uint8_t temp, value;

    uint8_t i;
    for(;;) {
        if (lastValue != value) {
            for (i = 0; i < 4; i++) {
                PORTD |= (1 << PD4);
                UART_puti(value);
                _delay_ms(20);
                lastValue = value;
            }
            PORTD &= ~(1 << PD4);
            if (value != 0) {
                sleepValue = value;
            } else {
                sleepMode();
            }
        }
        //if (!TWI_TransceiverBusy()) {
        //    //PORTD |= (1 << PD7);
        //    if (TWI_statusReg.RxDataInBuf) {
        //        TWI_GetDataFromTransceiver(&temp, 1);
        //    }
        //    TWI_StartTransceiverWithData(&temp, 1);
        //}
        //PORTD ^= (1 << PD4);
        //UART_puts("ahoj");
        //UART_putc('\n');
    }
}

void watchDogInit(void) {
    // Watch dog every 0.25s and power down
    WDTCSR |= (1 << WDP2);
    WDTCSR |= (1 << WDIE);
}

void pinsInit(void) {
    DDRD = 0x00;
    PORTD = 0x00;
    DDRD |= (1 << PD4);

    DDRC = 0x00;
    PORTC = 0x00;

    // all B pins as input
    DDRB = 0x00;
    PORTB = 0x00;
}

void readAddress(volatile uint8_t *port, volatile uint8_t *addr) {

    if(bit_is_set(*port, PB0)) {
        *addr = (1 << 0);
    }
    if(bit_is_set(*port, PB1)) {
        *addr |= (1 << 1);
    }
    if(bit_is_set(*port, PB2)) {
        *addr |= (1 << 2);
    }
    if(bit_is_set(*port, PB3)) {
        *addr |= (1 << 3);
    }
    if(bit_is_set(*port, PB4)) {
        *addr |= (1 << 4);
    }
    if(bit_is_set(*port, PB5)) {
        *addr |= (1 << 5);
    }
    if(bit_is_set(*port, PB6)) {
        *addr |= (1 << 6);
    }
    if(bit_is_set(*port, PB7)) {
        *addr |= (1 << 7);
    }
}

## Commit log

2014-02-07 experimenty
2014-02-07 modified
2014-02-10 measurment into timer attempt
2014-02-10 resolve release problem
2014-03-09 sleep mode
2014-07-26 add version for mega16
2014-07-26 add schema and board for m16
2014-10-14 version 2.0
2014-12-16 sens
2015-01-07 add web
2015-01-13 add booster
2015-01-21 add socket io
2015-01-27 new socket library
2015-01-28 packages
2015-01-28 packaging
2016-08-17 initial add light
2016-12-30 final version

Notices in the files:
parts and their libraries:
sparkfun: Licensing: CC v3.0 Share-Alike You are welcome to use this library for commercial purposes.
